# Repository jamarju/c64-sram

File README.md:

# Commodore 64 (C64C) SRAM replacement

This is a static RAM replacement for C64C chips U10 and U11 (motherboards assy no. 250469).

It may also work on assy no. 250466 (DRAM chips U9 and U10), but I have only tested it on a 250469 board.

It is based on [Gerrit4's design, originally posted at the lemon64 forum](http://www.lemon64.com/forum/viewtopic.php?p=773935#773935).

## Building

See [bom](bom/) and [gerber](gerber/) if you wish to build your own.

You can use any pin headers you find suitable but I suggest 0.50 mm round pin headers so as not to put too much stress on the sockets. They are easy to find on Aliexpress as "gold round male pin".

You can solder all 36 pins of U10 and U11 as in the pictures below, however only these 23 pins are strictly needed:

* U10: pins 2, 3, 15, 17, 18
* U11: all pins required

For soldering convenience and better board support I suggest soldering the following:

* U10: solder pins 2, 3, 15, 16, 17, 18
* U11: solder all pins

## Thanks

Gerrit4 for the schematic design.

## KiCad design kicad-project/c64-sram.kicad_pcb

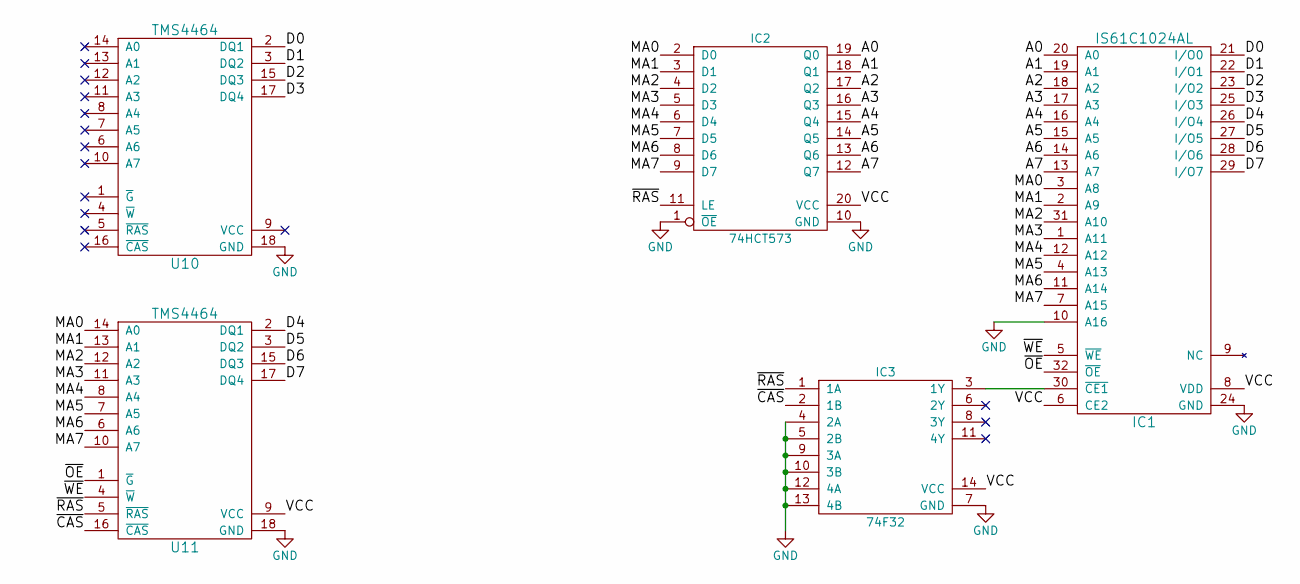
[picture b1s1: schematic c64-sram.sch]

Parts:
IC1: IS61C1024AL; TSOP_I_32L_8x20_p0.5
IC2: 74HCT573; TSSOP20_4.4x6.3_p0.65
IC3: 74F32; SOIC-14_6x8.65
U10, U11: TMS4464; DIP-18_W7.62mm_LongPads

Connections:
/A0: IC1.20 (A0), IC2.19 (Q0)
/A1: IC1.19 (A1), IC2.18 (Q1)
/A2: IC1.18 (A2), IC2.17 (Q2)
/A3: IC1.17 (A3), IC2.16 (Q3)
/A4: IC1.16 (A4), IC2.15 (Q4)
/A5: IC1.15 (A5), IC2.14 (Q5)
/A6: IC1.14 (A6), IC2.13 (Q6)
/A7: IC1.13 (A7), IC2.12 (Q7)
/D0: IC1.21 (I/O0), U10.2 (DQ1)
/D1: IC1.22 (I/O1), U10.3 (DQ2)
/D2: IC1.23 (I/O2), U10.15 (DQ3)
/D3: IC1.25 (I/O3), U10.17 (DQ4)
/D4: IC1.26 (I/O4), U11.2 (DQ1)
/D5: IC1.27 (I/O5), U11.3 (DQ2)
/D6: IC1.28 (I/O6), U11.15 (DQ3)
/D7: IC1.29 (I/O7), U11.17 (DQ4)
/MA0: IC1.3 (A8), IC2.2 (D0), U11.14 (A0)
/MA1: IC1.2 (A9), IC2.3 (D1), U11.13 (A1)
/MA2: IC1.31 (A10), IC2.4 (D2), U11.12 (A2)
/MA3: IC1.1 (A11), IC2.5 (D3), U11.11 (A3)
/MA4: IC1.12 (A12), IC2.6 (D4), U11.8 (A4)
/MA5: IC1.4 (A13), IC2.7 (D5), U11.7 (A5)
/MA6: IC1.11 (A14), IC2.8 (D6), U11.6 (A6)
/MA7: IC1.7 (A15), IC2.9 (D7), U11.10 (A7)
/VCC: IC1.6 (CE2), IC1.8 (VDD), IC2.20 (VCC), IC3.14 (VCC), U11.9 (VCC)
/~CAS: IC3.2 (1B), U11.16 (~CAS)
/~OE: IC1.32 (~OE), U11.1 (~G)
/~RAS: IC2.11 (LE), IC3.1 (1A), U11.5 (~RAS)
/~WE: IC1.5 (~WE), U11.4 (~W)
GND: IC1.10 (A16), IC1.24 (GND), IC2.1 (~OE), IC2.10 (GND), IC3.4 (2A), IC3.5 (2B), IC3.7 (GND), IC3.9 (3A), IC3.10 (3B), IC3.12 (4A), IC3.13 (4B), U10.18 (GND), U11.18 (GND)
unnamed: IC1.30 (~CE1), IC3.3 (1Y)

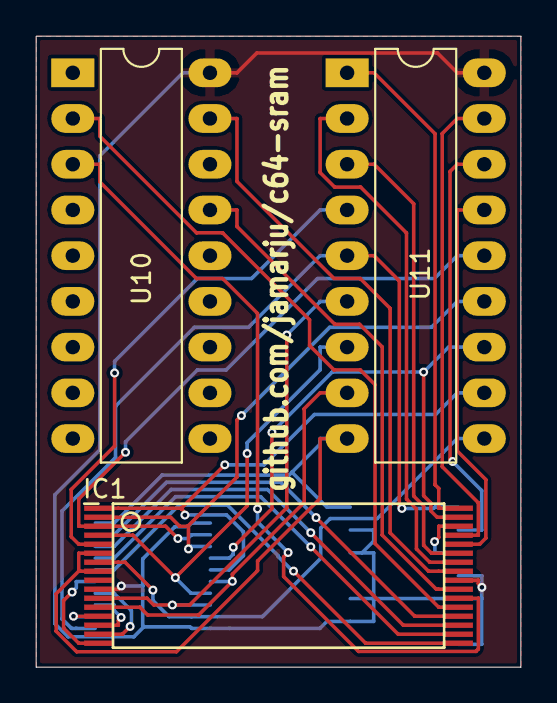
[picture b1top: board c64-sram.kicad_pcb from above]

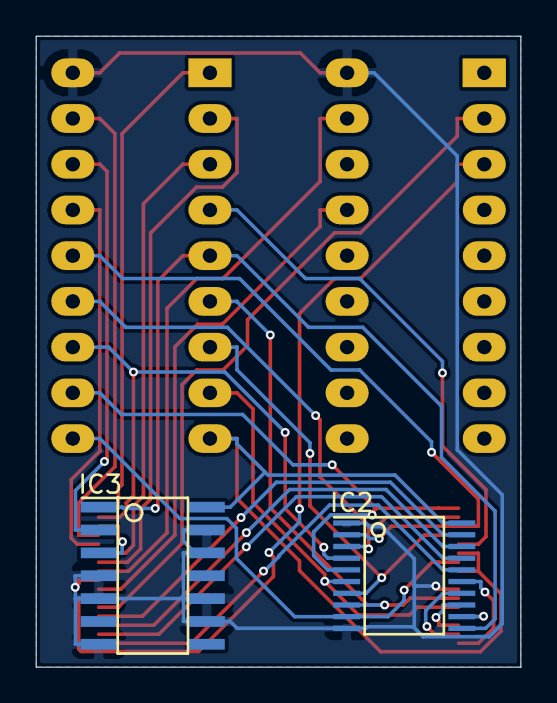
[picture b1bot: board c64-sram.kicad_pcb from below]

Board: 2 copper layers, 26.9 x 35.1 mm, 5 parts (2 on the bottom side), 31 nets.

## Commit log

2018-03-25 pin header soldering suggestions
2018-03-26 pin header provider suggestions
